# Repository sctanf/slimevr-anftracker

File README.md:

# slimevr-anftracker

Most recent designs are in module-35mm

Unfinished for now

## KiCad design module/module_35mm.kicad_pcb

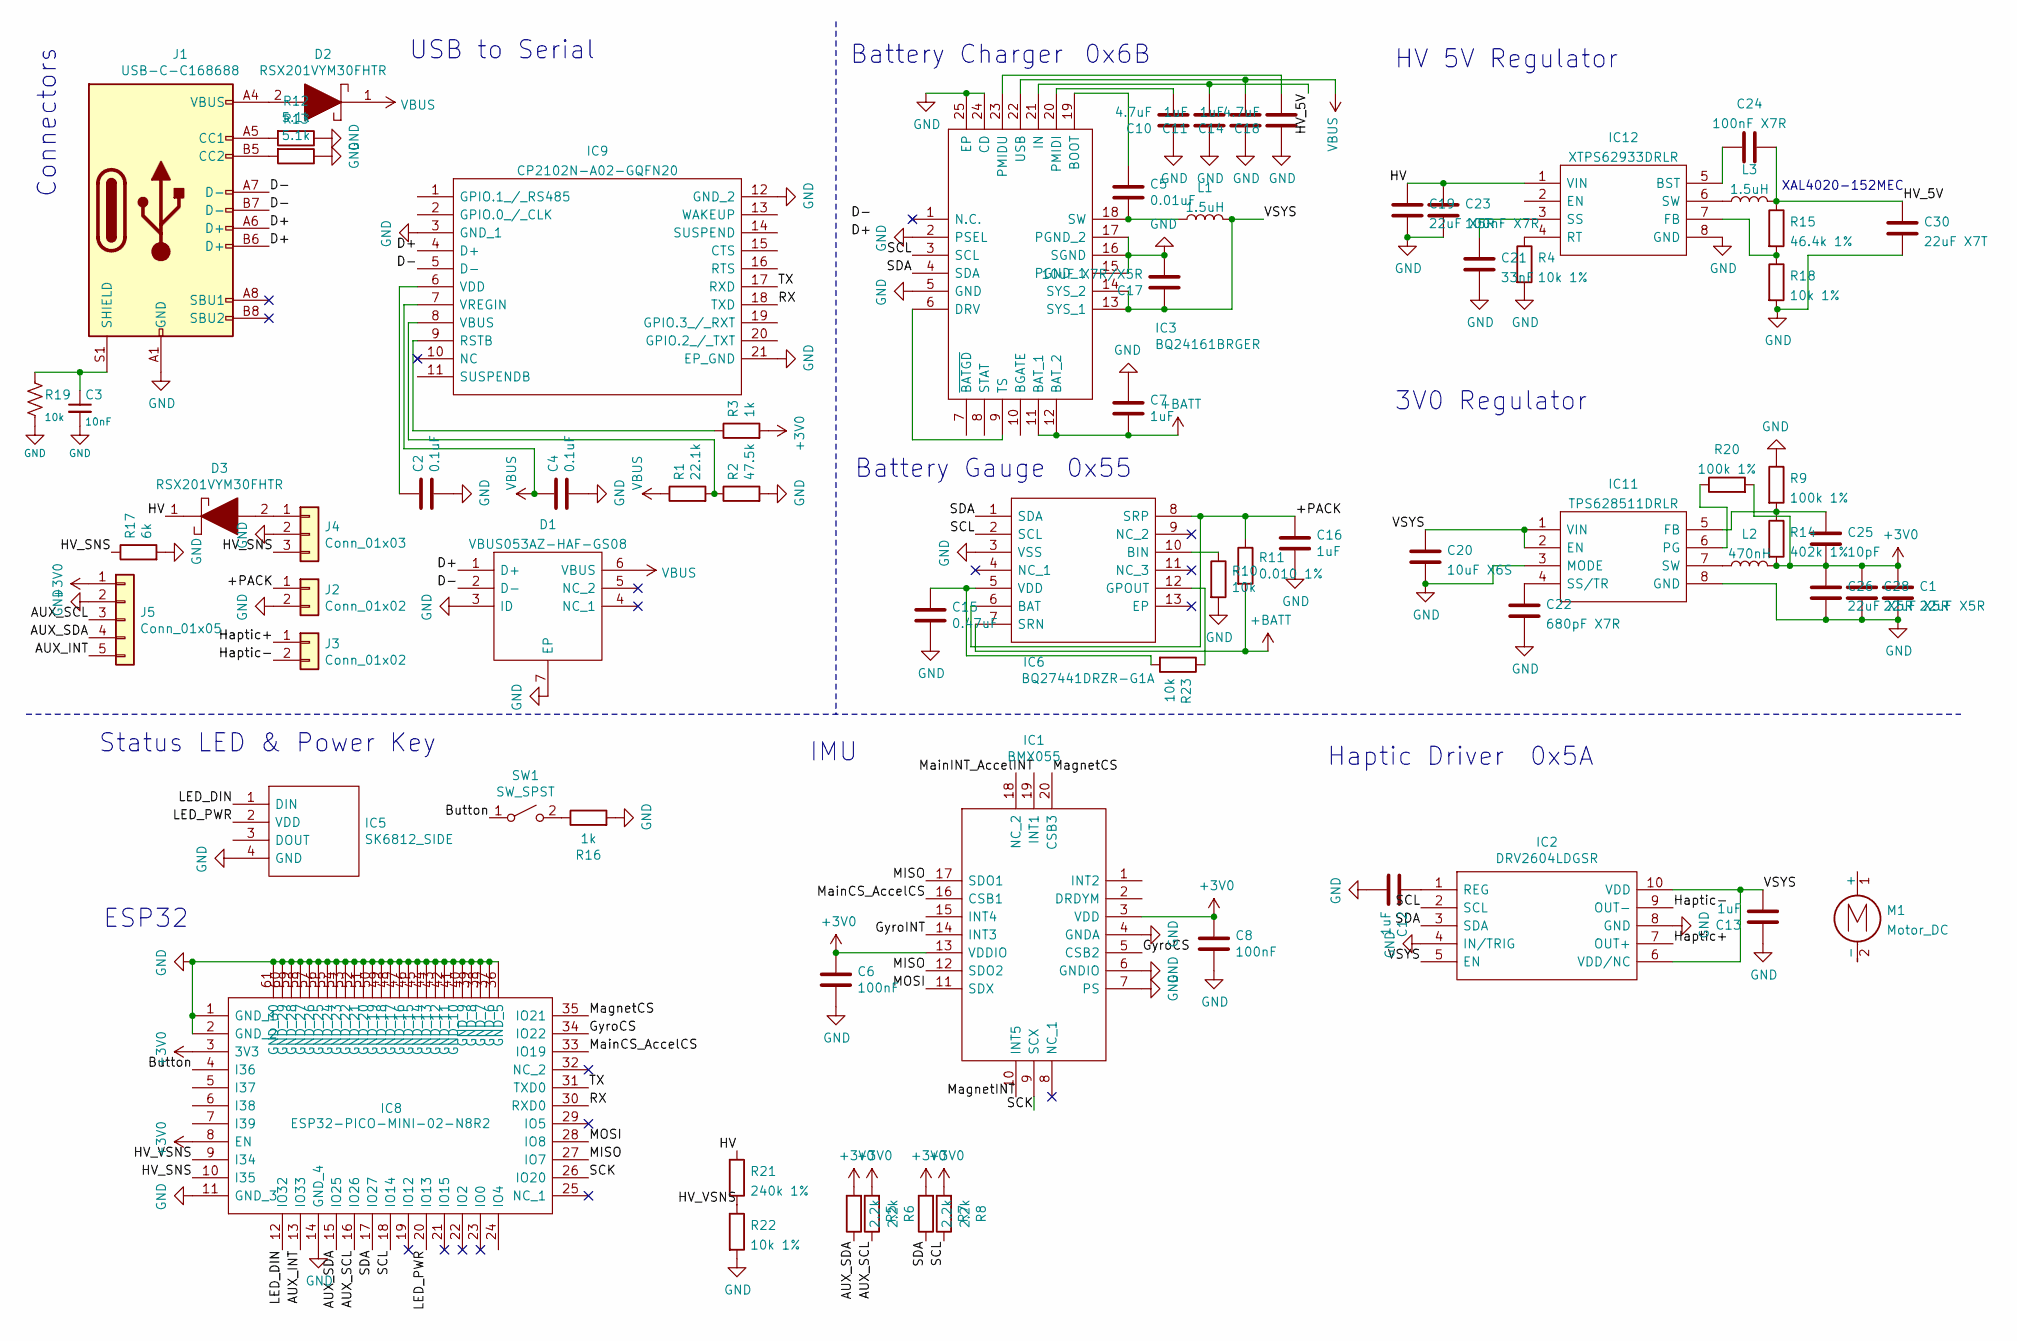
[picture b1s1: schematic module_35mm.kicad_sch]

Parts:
C1, C26, C28: 22uF X5R; C_0603_1608Metric
C2, C4: 0.1uF; C_0402_1005Metric
C3: 10nF; C_0402_1005Metric
C5: 0.01uF; C_0402_1005Metric
C6, C8: 100nF; C_0402_1005Metric
C7, C11, C12, C13, C14, C16: 1uF; C_0402_1005Metric
C10, C18: 4.7uF; C_0402_1005Metric
C15: 0.47uF; C_0402_1005Metric
C17: 10uF X7R/X5R; C_0603_1608Metric
C19: 22uF X5R; C_1206_3216Metric
C20: 10uF X6S; C_0603_1608Metric
C21: 33nF; C_0402_1005Metric
C22: 680pF X7R; C_0402_1005Metric
C23, C24: 100nF X7R; C_0402_1005Metric
C25: 10pF; C_0402_1005Metric
C30: 22uF X7T; C_0805_2012Metric
D1: VBUS053AZ-HAF-GS08; SON50P160X160X60-7N; Mouser Part Number 78-VBUS053AZ-HAF
D2, D3: RSX201VYM30FHTR; Mouser Part Number 755-RSX201VYM30FHTR
IC1: BMX055; Manufacturer_Part_Number BMX055; Mouser Part Number 262-BMX055
IC2: DRV2604LDGSR; SOP50P490X110-10N; Manufacturer_Part_Number DRV2604LDGSR; Mouser Part Number 595-DRV2604LDGSR
IC3: BQ24161BRGER; QFN50P400X400X100-25N-D; Manufacturer_Part_Number BQ24161BRGER; Mouser Part Number 595-BQ24161BRGER
IC5: SK6812_SIDE; SK6812SIDE; Manufacturer_Part_Number SK6812 SIDE
IC6: BQ27441DRZR-G1A; BQ27441DRZRG1A; Mouser Part Number 595-BQ27441DRZR-G1A
IC8: ESP32-PICO-MINI-02-N8R2; ESP32PICOMINI02N8R2; Mouser Part Number 356-ESP32PCOMN2PH3Q0
IC9: CP2102N-A02-GQFN20; CP2102NA02GQFN20; Mouser Part Number 634-CP2102NA02GQFN20
IC11: TPS628511DRLR; SOTFL50P160X60-8N; Manufacturer_Part_Number TPS628511DRLR
IC12: XTPS62933DRLR; SOTFL50P160X60-8N; Manufacturer_Part_Number TPS628511DRLR
J1: USB-C-C168688
J2, J3: Conn_01x02; ACHL
J4: Conn_01x03; JST_SUR_SM03B-SURS-TF_1x03-1MP_P0.80mm_Horizontal
J5: Conn_01x05; JST_SUR_SM05B-SURS-TF_1x05-1MP_P0.80mm_Horizontal
L1: 1.5uH; INDPM4441X120N
L2: 470nH; L_0603_1608Metric
L3: 1.5uH; XAL4020152MEB
M1: Motor_DC; 10x10x4mm LRA
R1: 22.1k; R_0402_1005Metric
R2: 47.5k; R_0402_1005Metric
R3, R16: 1k; R_0402_1005Metric
R4, R18, R22: 10k 1%; R_0402_1005Metric
R5, R6, R7, R8: 2.2k; R_0402_1005Metric
R9, R20: 100k 1%; R_0402_1005Metric
R10, R19, R23: 10k; R_0402_1005Metric
R11: 0.010 1%; R_0402_1005Metric
R12, R13: 5.1k; R_0402_1005Metric
R14: 402k 1%; R_0402_1005Metric
R15: 46.4k 1%; R_0402_1005Metric
R17: 6k; R_0402_1005Metric
R21: 240k 1%; R_0402_1005Metric
SW1: SW_SPST; TCD-C2KQR

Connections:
+3V0: C1.1, C6.1, C8.1, C25.2, C26.1, C28.1, IC1.3 (VDD), IC1.13 (VDDIO), IC8.3 (3V3), IC8.8 (EN), J5.1, L2.2, R3.2, R5.2, R6.2, R7.2, R8.2, R14.2, R20.2
+BATT: C7.2, IC3.11 (BAT_1), IC3.12 (BAT_2), IC6.7 (SRN), R11.2
/+PACK: C16.1, IC6.6 (BAT), IC6.8 (SRP), J2.1, R11.1
/AUX_INT: IC8.13 (IO33), J5.5
/AUX_SCL: IC8.16 (IO26), J5.3, R6.1
/AUX_SDA: IC8.15 (IO25), J5.4, R5.1
/Button: IC8.4 (I36), SW1.1 (A)
/D+: D1.1 (D+), IC9.4 (D+), J1.A6 (D+), J1.B6 (D+)
/D-: D1.2 (D-), IC9.5 (D-), J1.A7 (D-), J1.B7 (D-)
/GyroCS: IC1.5 (CSB2), IC8.34 (IO22)
/HV: C19.1, C23.1, D3.1, IC12.1 (VIN), R21.1
/HV_5V: C11.2, C24.2, C30.1, IC3.21 (IN), L3.2, R15.1
/HV_SNS: IC8.10 (I35), J4.3, R17.1
/HV_VSNS: IC8.9 (I34), R21.2, R22.1
/Haptic+: IC2.7 (OUT+), J3.1
/Haptic-: IC2.9 (OUT-), J3.2
/LED_DIN: IC5.1 (DIN), IC8.12 (IO32)
/LED_PWR: IC5.2 (VDD), IC8.20 (IO13)
/MISO: IC1.12 (SDO2), IC1.17 (SDO1), IC8.27 (IO7)
/MOSI: IC1.11 (SDX), IC8.28 (IO8)
/MagnetCS: IC1.20 (CSB3), IC8.35 (IO21)
/MainCS_AccelCS: IC1.16 (CSB1), IC8.33 (IO19)
/RX: IC8.30 (RXD0), IC9.18 (TXD)
/SCK: IC1.9 (SCX), IC8.26 (IO20)
/SCL: IC2.2 (SCL), IC3.3 (SCL), IC6.2 (SCL), IC8.18 (IO14), R8.1
/SDA: IC2.3 (SDA), IC3.4 (SDA), IC6.1 (SDA), IC8.17 (IO27), R7.1
/TX: IC8.31 (TXD0), IC9.17 (RXD)
/VSYS: C13.2, C17.1, C20.1, IC2.5 (EN), IC2.6 (VDD/NC), IC2.10 (VDD), IC3.13 (SYS_1), IC3.14 (SYS_2), IC11.1 (VIN), IC11.2 (EN), L1.2
GND: C1.2, C2.2, C3.2, C4.2, C6.2, C7.1, C8.2, C10.1, C11.1, C12.2, C13.1, C14.1, C15.2, C16.2, C17.2, C18.1, C19.2, C20.2, C21.2, C22.2, C23.2, C26.2, C28.2, C30.2, D1.3 (ID), D1.7 (EP), IC1.4 (GNDA), IC1.6 (GNDIO), IC1.7 (PS), IC2.4 (IN/TRIG), IC2.8 (GND), IC3.2 (PSEL), IC3.5 (GND), IC3.15 (PGND_1), IC3.16 (SGND), IC3.17 (PGND_2), IC3.24 (CD), IC3.25 (EP), IC5.4 (GND), IC6.3 (VSS), IC8.1 (GND_1), IC8.2 (GND_2), IC8.11 (GND_3), IC8.14 (GND_4), IC8.36 (GND_5), IC8.37 (GND_6), IC8.38 (GND_7), IC8.39 (GND_8), IC8.40 (GND_9), IC8.41 (GND_10), IC8.42 (GND_11), IC8.43 (GND_12), IC8.44 (GND_13), IC8.45 (GND_14), IC8.46 (GND_15), IC8.47 (GND_16), IC8.48 (GND_17), IC8.49 (GND_18), IC8.50 (GND_19), IC8.51 (GND_20), IC8.52 (GND_21), IC8.53 (GND_22), IC8.54 (GND_23), IC8.55 (GND_24), IC8.56 (GND_25), IC8.57 (GND_26), IC8.58 (GND_27), IC8.59 (GND_28), IC8.60 (GND_29), IC8.61 (GND_30), IC9.3 (GND_1), IC9.12 (GND_2), IC9.21 (EP_GND), IC11.3 (MODE), IC11.8 (GND), IC12.8 (GND), J1.A1 (GND), J2.2, J4.2, J5.2, R2.2, R4.2, R9.1, R10.2, R12.1, R13.1, R16.2, R17.2, R18.2, R19.2, R22.2
unnamed: C2.1, IC9.6 (VDD)
unnamed: C3.1, J1.S1 (SHIELD), R19.1
unnamed: C5.1, IC3.19 (BOOT)
unnamed: C5.2, IC3.18 (SW), L1.1
unnamed: C10.2, IC3.20 (PMIDI)
unnamed: C12.1, IC2.1 (REG)
unnamed: C15.1, IC6.5 (VDD), R23.2
unnamed: C18.2, IC3.23 (PMIDU)
unnamed: C21.1, IC12.3 (SS)
unnamed: C22.1, IC11.4 (SS/TR)
unnamed: C24.1, IC12.5 (BST)
unnamed: C25.1, IC11.5 (FB), R9.2, R14.1
unnamed: D2.2, J1.A4 (VBUS)
unnamed: D3.2, J4.1
unnamed: IC3.6 (DRV), IC3.9 (TS)
unnamed: IC6.10 (BIN), R10.1
unnamed: IC6.12 (GPOUT), R23.1
unnamed: IC9.8 (VBUS), R1.2, R2.1
unnamed: IC9.9 (RSTB), R3.1
unnamed: IC11.6 (PG), R20.1
unnamed: IC11.7 (SW), L2.1
unnamed: IC12.4 (RT), R4.1
unnamed: IC12.6 (SW), L3.1
unnamed: IC12.7 (FB), R15.2, R18.1
unnamed: J1.A5 (CC1), R12.2
unnamed: J1.B5 (CC2), R13.2
unnamed: R16.1, SW1.2 (B)
VBUS: C4.1, C14.2, D1.6 (VBUS), D2.1, IC3.22 (USB), IC9.7 (VREGIN), R1.1

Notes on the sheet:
Connectors
Status LED & Power Key
ESP32
USB to Serial
IMU
Battery Charger
Battery Gauge
0x55
0x6B
Haptic Driver
HV 5V Regulator
3V0 Regulator
0x5A
XAL4020-152MEC

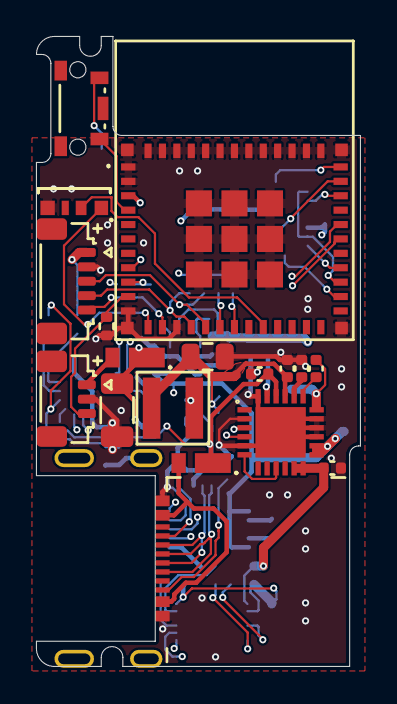
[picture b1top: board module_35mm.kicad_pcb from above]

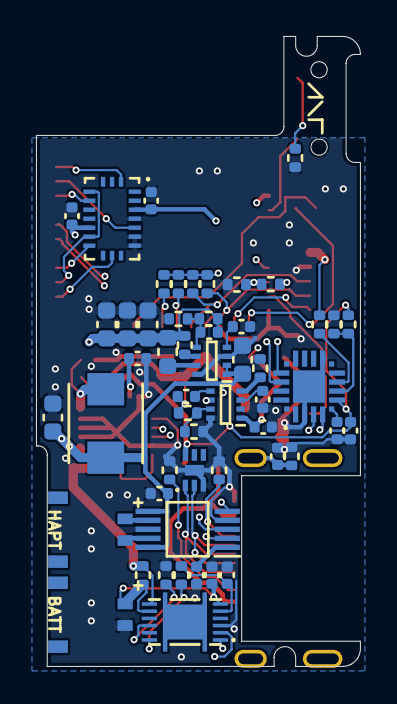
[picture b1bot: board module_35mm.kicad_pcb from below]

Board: 4 copper layers, 18.0 x 35.0 mm, 72 parts (53 on the bottom side), 57 nets.

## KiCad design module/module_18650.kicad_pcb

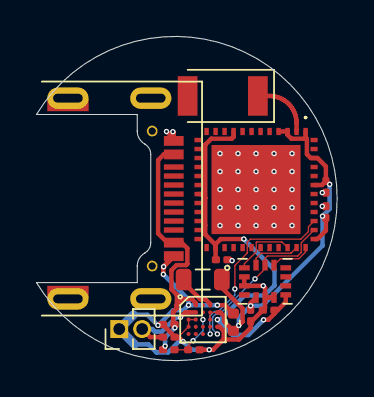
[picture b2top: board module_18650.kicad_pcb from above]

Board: 2 copper layers, 16.7 x 18.0 mm, 17 parts (0 on the bottom side), 13 nets.

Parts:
C4, C8, C9, C12: 0.1uF; C_0201_0603Metric
C5: 10uF; C_0402_1005Metric
C6, C7, C11: 1uF; C_0201_0603Metric
IC1: BMX160; PQFN50P300X250X88-14N
IC3: ESP32-PICO-V3; ESP32PICOV3
IC4: BQ25125YFPR; BGA25C40P5X5_247X253X50
J1: NN01-110; ANTC4120X120N
J2: USB-C-C168688; Mid_Mount-USB_C
J3: Conn_01x02; PinHeader_1x02_P1.27mm_Vertical
L2: 2.2uH; L_0805_2012Metric
R1: 14k; R_0201_0603Metric
R2: 14.3k; R_0201_0603Metric

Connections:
+3.3VA: C9.1, C12.1, IC1.8, IC3.9, IC3.19, IC3.26, IC4.C5
+3V0: C4.1, C5.1, C8.1, C11.1, IC1.5, IC3.1, IC3.3, IC3.4, IC3.37, IC3.43, IC3.46, IC4.B4, IC4.B5, IC4.C4, L2.1
+BATT: C6.1, IC4.B1, IC4.B2, J3.2
/CS: IC1.12, IC3.36
/SCK: IC1.13, IC3.38, IC4.E5
/SDA: IC3.39, IC4.E4
/SDI: IC1.14, IC3.35
/SDO: IC1.1, IC3.34
GND: C4.2, C5.2, C6.2, C7.1, C8.2, C9.2, C11.2, C12.2, IC1.2, IC1.3, IC1.6, IC1.7, IC3.49, IC4.A1, IC4.A5, IC4.C1, IC4.C2, IC4.D1, IC4.D5, J2.A1, J3.1, R2.2
unnamed: IC3.2, J1.1
unnamed: IC4.A4, L2.2
unnamed: IC4.C3, R1.2, R2.1
VCC: C7.2, IC4.A2, J2.A4, R1.1

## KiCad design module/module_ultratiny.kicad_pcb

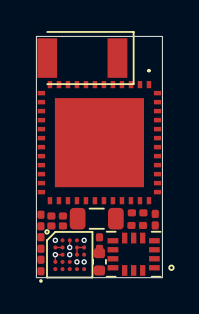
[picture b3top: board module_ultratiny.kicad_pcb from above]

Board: 2 copper layers, 7.0 x 13.4 mm, 15 parts (0 on the bottom side), 10 nets.

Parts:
C3, C4, C8, C9: 0.1uF; C_0201_0603Metric
C5: 10uF; C_0402_1005Metric
C6, C7: 1uF; C_0201_0603Metric
D1: LED; LED_0201_0603Metric
IC1: BMX160; PQFN50P300X250X88-14N
IC3: ESP32-PICO-V3; ESP32PICOV3
IC4: BQ25125YFPR; BGA25C40P5X5_247X253X50
J1: NN01-110; ANTC4120X120N
L2: 2.2uH; L_0805_2012Metric
R1: 14k; R_0201_0603Metric
R2: 14.3k; R_0201_0603Metric

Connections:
+3V0: C3.1, C4.1, C5.1, C9.1, IC1.8, IC3.1, IC3.3, IC3.4, IC3.19, IC3.37, IC3.43, IC3.46, IC4.B4, IC4.B5, IC4.C4, L2.1
GND: C3.2, C4.2, C5.2, C6.2, C7.1, C8.2, C9.2, IC1.2, IC1.3, IC1.6, IC1.7, IC3.49, IC4.A1, IC4.A5, IC4.C1, IC4.C2, IC4.D1, IC4.D5, R2.2
unnamed: C6.1, IC4.B1, IC4.B2
unnamed: C8.1, IC1.5
unnamed: D1.1, IC4.D4
unnamed: D1.2, IC4.A3, IC4.B3
unnamed: IC3.2, J1.1
unnamed: IC4.A4, L2.2
unnamed: IC4.C3, R1.2, R2.1
VCC: C7.2, IC4.A2, R1.1
